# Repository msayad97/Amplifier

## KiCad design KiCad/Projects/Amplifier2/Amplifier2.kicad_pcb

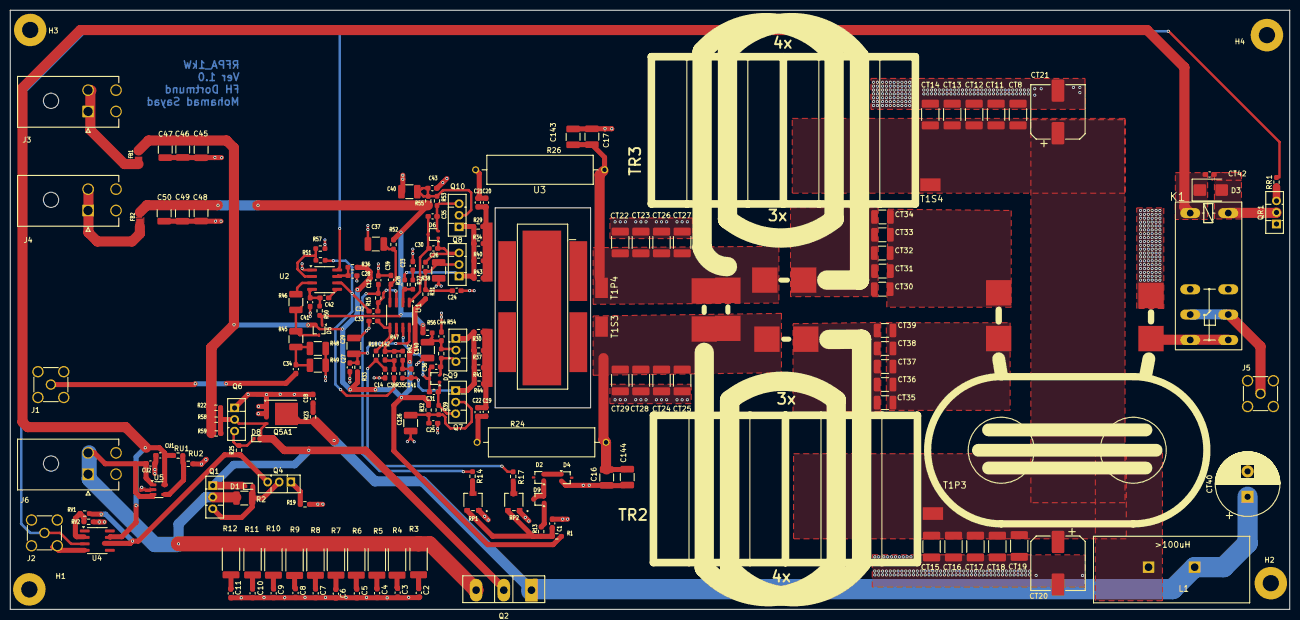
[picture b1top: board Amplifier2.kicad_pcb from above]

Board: 4 copper layers, 252.0 x 118.0 mm, 196 parts (0 on the bottom side), 80 nets.

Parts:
C1, C2, C3, C4, C5, C6, C7, C8, C9, C10, C11, C12, C14, C23, C24, C25, C27, C28, C30, C31, C32, C33, C35, C36, C38, C39, C41, C43, C44: 0.1uF; C_0603_1608Metric_Pad1.08x0.95mm_HandSolder
C16, C17, C143, C144: 470p; C_1210_3225Metric_Pad1.33x2.70mm_HandSolder
C18, C19, C20: 1nF; C_0603_1608Metric_Pad1.08x0.95mm_HandSolder
C21, C22: DNA; C_0603_1608Metric_Pad1.08x0.95mm_HandSolder
C26, C29, C37, C40, C45, C46, C47, C48, C49, C50, C126, C140: 10uF; C_1210_3225Metric_Pad1.33x2.70mm_HandSolder
C34: 4n7; C_0603_1608Metric_Pad1.08x0.95mm_HandSolder
C42, C141: 10p; C_0603_1608Metric_Pad1.08x0.95mm_HandSolder
C142: NDA; C_0603_1608Metric_Pad1.08x0.95mm_HandSolder
CT8, CT11, CT15, CT16: 10n; C_1812_4532Metric_Pad1.57x3.40mm_HandSolder
CT12, CT13, CT17, CT18: 100n; C_1812_4532Metric_Pad1.57x3.40mm_HandSolder
CT14, CT19: 1u; C_1812_4532Metric_Pad1.57x3.40mm_HandSolder
CT20, CT21: 100u/63; CP_Elec_10x10.5
CT22, CT23, CT24, CT25, CT26, CT27, CT28, CT29: 120p; C_1812_4532Metric_Pad1.57x3.40mm_HandSolder
CT30, CT31, CT32, CT33, CT34, CT35, CT36, CT37, CT38, CT39: 10n; C_1210_3225Metric_Pad1.33x2.70mm_HandSolder
CT40: 470u/63; CP_Radial_D12.5mm_P5.00mm
CT42: 100n; C_0603_1608Metric_Pad1.08x0.95mm_HandSolder
CU1, CU2: 1uF; C_0603_1608Metric_Pad1.08x0.95mm_HandSolder
D1, D8: BAT54XV2T5G; D_SOD-523_new
D2, D4, D5, D6, D7, D9: BAV99WT1G; SOT-323_SC-70
D3: D; D_SMB
FB1, FB2: FerriteBead; BLM21PG300SN1B
H1, H2, H3, H4: MountingHole; MountingHole_3.2mm_M3_Pad
J1: Input; SMA_Amphenol_901-144_Vertical
J2: Enable; SMA_Amphenol_901-144_Vertical
J3: Vp_8V; MOLEX_26013115
J4: Vn_-5V; MOLEX_26013115
J5: Output; SMA_Amphenol_901-144_Vertical
J6: Input_56V; MOLEX_26013115
K1: G2RE
L1: >100uH; KERN90_STEHEND_2PIN
Q1, Q4, Q6, Q7, Q8: BD139; TO-126-3_Vertical
Q2: IXTH90P10P; TO-247-3_MOSFET
Q5A1: BSC340N08NS3G; TDSON-8-1
Q9, Q10: BD140; TO-126-3_Vertical
QR1: BD139; TO-126-3_Vertical
R1, R15, R18, R25: 4k7; R_0603_1608Metric_Pad0.98x0.95mm_HandSolder
R2: 330R; R_1210_3225Metric_Pad1.30x2.65mm_HandSolder
R3, R4, R5, R6, R7, R8, R9, R10, R11, R12: 2R2; R_2512_6332Metric_Pad1.40x3.35mm_HandSolder
R13, R14, R17, R19: 120R; R_0603_1608Metric_Pad0.98x0.95mm_HandSolder
R22, R35, R42, R47, R58, R59: 220R; R_0603_1608Metric_Pad0.98x0.95mm_HandSolder
R23, R31, R32, R33, R36, R50, R52, R55, R56: 2R2; R_0603_1608Metric_Pad0.98x0.95mm_HandSolder
R24, R26: 270R; AX_1.000X.225_.034
R27, R28, R51, R57: 470R; R_0603_1608Metric_Pad0.98x0.95mm_HandSolder
R29, R30, R34, R37, R40, R41, R43, R44: 39R; R_0603_1608Metric_Pad0.98x0.95mm_HandSolder
R38, R39, R53, R54: 10k; R_0603_1608Metric_Pad0.98x0.95mm_HandSolder
R45, R46, R48, R49: 100R; R_1210_3225Metric_Pad1.30x2.65mm_HandSolder
RP1, RP2: R_Potentiometer; PVG3A
RR1: 1K; R_0603_1608Metric_Pad0.98x0.95mm_HandSolder
RU1: 25.2k; R_0603_1608Metric_Pad0.98x0.95mm_HandSolder
RU2: 1.35k; R_0603_1608Metric_Pad0.98x0.95mm_HandSolder
RV1: 10k; R_0603_1608Metric_Pad0.98x0.95mm_HandSolder
RV2: 2k; R_0603_1608Metric_Pad0.98x0.95mm_HandSolder
T1P3, T1P4, T1S3, T1S4: THICKPINSMD2,5X4; SMDPAD2,5X4
TR2: DOPPELRINGKERN
TR3: DOPPELRINGKERN_REV
TR4: BALUN; DOPPELLMANTEL_STEHEND
U1: AD8017ARZ; SOIC-8_3.9x4.9mm_P1.27mm
U2: AD8021AR; SOIC-8_3.9x4.9mm_P1.27mm
U3: BLF188XRU; BLF188
U4: AD8033; SOIC-8_3.9x4.9mm_P1.27mm
U5: LT3014xS5; SOT-23-5

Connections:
/HF Part/OutP1: CT30.2, CT31.2, CT32.2, CT33.2, CT34.2, TR3.S2
/HF Part/OutP2: CT35.2, CT36.2, CT37.2, CT38.2, CT39.2, TR2.S2
/HF Part/OutS1: CT30.1, CT31.1, CT32.1, CT33.1, CT34.1, TR4.S2
/HF Part/OutS2: CT35.1, CT36.1, CT37.1, CT38.1, CT39.1, TR4.P2
/HF Part/RFB1: C20.2, C21.2, R26.2
/HF Part/RFB2: C19.2, C22.2, R24.2
/Switch/ENA: Q4.3 (B), R25.1, RV1.1, U4.6
/Switch/G: D1.1 (A), D8.2 (K), Q1.1 (E), Q2.1 (G), Q5A1.4 (G), Q6.2 (C), R22.2, R58.2, R59.2
D1: C17.2, C143.2, CT22.1, CT23.1, CT26.1, CT27.1, R26.1, T1P4.P$1 (1), TR2.P1, TR3.P2, TR3.S1, U3.1 (D1)
D2: C16.2, C144.2, CT24.2, CT25.2, CT28.2, CT29.2, R24.1, T1S3.P$1 (1), TR2.P2, TR2.S1, TR3.P1, U3.2 (D2)
Enable: J2.1 (In), RR1.2, U2.8 (~DISABLE), U4.3 (+)
GND: C1.2, C2.2, C3.2, C4.2, C5.2, C6.2, C7.2, C8.2, C9.2, C10.2, C11.2, C12.2, C14.2, C16.1, C17.1, C18.2, C23.2, C24.2, C25.2, C26.2, C27.2, C28.2, C29.2, C33.1, C37.2, C39.2, C40.2, C41.2, C43.2, C44.2, C45.2, C46.2, C47.2, C48.2, C49.2, C50.2, C126.2, C140.2, C143.1, C144.1, CT8.2, CT11.2, CT12.2, CT13.2, CT14.2, CT15.2, CT16.2, CT17.2, CT18.2, CT19.2, CT20.2, CT21.2, CT22.2, CT23.2, CT24.1, CT25.1, CT26.2, CT27.2, CT28.1, CT29.1, CT40.2, CU1.2, CU2.2, D4.2 (A), J1.2 (Ext), J2.2 (Ext), J3.3, J3.4, J4.3, J4.4, J5.2 (Ext), J6.3, J6.4, K1.O0 (O), K1.O1 (O@1), Q5A1.1 (S), Q5A1.2 (S), Q5A1.3 (S), Q6.1 (E), QR1.1 (E), R19.2, R48.2, R49.2, R57.1, RP1.3, RP2.3, RU2.2, RV2.2, TR4.S1, U2.1 (LOGIC_REFERENCE), U3.5 (S), U4.4 (V-), U5.2 (GND)
Input_56V: CU2.1, J6.1, J6.2, Q1.2 (C), Q2.3 (S), R2.1, R3.1, R4.1, R5.1, R6.1, R7.1, R8.1, R9.1, R10.1, R11.1, R12.1, U5.1 (VIN), U5.3 (~SHDN)
Input_Signal: C34.1, J1.1 (In)
unnamed: C1.1, R1.1, R13.1, RP1.1, RP2.1
unnamed: C2.1, R3.2
unnamed: C3.1, R4.2
unnamed: C4.1, R5.2
unnamed: C5.1, R6.2
unnamed: C6.1, R7.2
unnamed: C7.1, R8.2
unnamed: C8.1, R9.2
unnamed: C9.1, R10.2
unnamed: C10.1, R11.2
unnamed: C11.1, R12.2
unnamed: C12.1, R14.1, R15.2
unnamed: C14.1, R17.1, R18.2
unnamed: C18.1, R23.2
unnamed: C23.1, R27.1
unnamed: C34.2, R45.2, R48.1, R49.1
unnamed: C141.1, R35.2, R42.1
unnamed: C38.2, C142.1, R47.2
unnamed: D1.2 (K), Q1.3 (B), Q4.2 (C), R2.2
unnamed: D2.2 (A), D4.1 (K)
unnamed: CT42.2, D3.2 (A), K1.2, QR1.2 (C)
unnamed: D5.3 (K), R45.1, R46.2
unnamed: C35.2, D6.2 (A), Q10.3 (B), R53.1
unnamed: C36.2, D7.2 (A), Q9.3 (B), R54.1
unnamed: D8.1 (A), Q6.3 (B), R25.2
unnamed: D2.1 (K), D9.2 (A), D9.3 (K)
unnamed: D9.1 (K), R13.2
unnamed: FB1.2, J3.1, J3.2
unnamed: FB2.2, J4.1, J4.2
unnamed: J5.1 (In), K1.P0 (P@1), K1.P1
unnamed: K1.S0 (S), K1.S1 (S@1), TR4.P1
unnamed: CT8.1, CT11.1, CT12.1, CT13.1, CT14.1, CT15.1, CT16.1, CT17.1, CT18.1, CT19.1, CT20.1, CT21.1, L1.P$2 (2), T1P3.P$1 (1), T1S4.P$1 (1)
unnamed: Q4.1 (E), R19.1
unnamed: C31.2, D7.1 (K), Q7.3 (B), R39.2
unnamed: C25.1, C126.1, Q7.2 (C), R32.1, R39.1
unnamed: C141.2, Q7.1 (E), Q9.1 (E), R30.2, R35.1, R37.2, R41.2, R44.2
unnamed: C30.2, D6.1 (K), Q8.3 (B), R38.2
unnamed: C24.1, C26.1, Q8.2 (C), R31.1, R38.1
unnamed: C44.1, C140.1, Q9.2 (C), R54.2, R56.1
unnamed: C40.1, C43.1, Q10.2 (C), R53.2, R55.1
unnamed: Q8.1 (E), Q10.1 (E), R28.2, R29.2, R34.2, R40.2, R43.2
unnamed: QR1.3 (B), RR1.1
unnamed: R14.2, RP1.2
unnamed: R17.2, RP2.2
unnamed: C27.1, C29.1, R33.1, U1.8 (+VS)
unnamed: R27.2, R28.1, U1.2 (-IN1)
unnamed: C142.2, R42.2, R47.1, U1.6 (-IN2)
unnamed: C37.1, C39.1, R52.1, U1.4 (-VS)
unnamed: C30.1, C35.1, D6.3 (K), U1.1 (OUT1)
unnamed: C31.1, C36.1, D7.3 (K), U1.7 (OUT2)
unnamed: R46.1, U2.3 (+)
unnamed: R51.1, R57.2, U2.2 (-)
unnamed: C42.1, U2.5 (C_{COMP})
unnamed: C28.1, R36.1, U2.7 (V+)
unnamed: C41.1, C42.2, R50.1, U2.4 (V-)
unnamed: RV1.2, RV2.1, U4.2 (-)
unnamed: RU1.2, RU2.1, U5.4 (ADJ)
Output_56V: CT40.1, L1.P$1 (1), Q2.2 (D), Q5A1.5 (D), R23.1
Output_OPV1: C32.1, C38.1, R51.2, U2.6
Output_OPV2_1: C20.1, C21.1, R29.1, R34.1, R40.1, R43.1, U3.3 (G1)
Output_OPV2_2: C19.1, C22.1, R30.1, R37.1, R41.1, R44.1, U3.4 (G2)
V_25V: CT42.1, CU1.1, D3.1 (K), K1.1, RU1.1, U4.7 (V+), U5.5 (VOUT)
Vn: C48.1, C49.1, C50.1, D5.1 (K), FB2.1, R50.2, R52.2, R55.2, R56.2
Vp: C45.1, C46.1, C47.1, D5.2 (A), FB1.1, R1.2, R22.1, R31.2, R32.2, R33.2, R36.2, R58.1, R59.1
bias1: C32.2, R15.1, U1.3 (+IN1)
bias2: C33.2, R18.1, U1.5 (+IN2)

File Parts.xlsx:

Name | Zahl | Value | Footprint | Link
Q2 | 1 | IXTH90P10P | TO247AA | https://www.mouser.de/ProductDetail/IXYS/IXTH90P10P?qs=cvHLL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
Q5 | 1 | BSC340N08NS3 | SO8_N | https://www.mouser.de/ProductDetail/Infineon-Technologies/BS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
Q1, Q4, Q6, Q7, Q8, QR1 | 6 | BD139 | SOT-32 | https://www.mouser.de/ProductDetail/STMicroelectronics/BD139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
Q9, Q10 | 2 | BD140 | SOT-32 | https://www.mouser.de/ProductDetail/STMicroelectronics/BD140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
D1, D8 | 2 | BAT54XV2T5G | ONSC-SOD-523 | https://www.mouser.de/ProductDetail/onsemi/BAT54XV2T5G?qs=Jh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
D2, D4, D5, D6, D7, D9 | 6 | BAV99WT1G | ONSC-SOT-323_SC-70 | https://www.mouser.de/ProductDetail/onsemi/BAV99WT1G?qs=vLkC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
D3 | 1 | Schottky Diode | SMA
U1 | 1 | AD8017ARZ | SOIC-8_3.9x4.9mm | https://www.mouser.de/ProductDetail/Analog-Devices/AD8017ARZ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
U2 | 1 | AD8021ARZ | SOIC-8_3.9x4.9mm | https://www.mouser.de/ProductDetail/Analog-Devices/AD8021ARZ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
U3 | 1 | BLF188XRU | SOT-539A | https://www.digikey.de/de/products/detail/ampleon-usa-inc/56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
U4 | 1 | AD8033 | SOIC-8_3.9x4.9mm | https://www.mouser.de/ProductDetail/Analog-Devices/AD8033ARZ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
U5 | 1 | LT3014xS5 | SOT-23-5 | https://www.mouser.de/ProductDetail/Analog-Devices/LT3014ES5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
U6 | 1 | LT1085-12 | SOT_THT:TO-220-3 | https://www.mouser.de/ProductDetail/Analog-Devices/LT1085CT-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
J3, J4, J6 | 3 | Molex Stecker | MOLEX_26013115 | https://www.mouser.de/ProductDetail/Molex/26-01-3115?qs=ZhwK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
J1, J2, J5 | 3 | Connector_Coaxial | SMA_Amphenol_901-144_Vertical | https://www.mouser.de/ProductDetail/Amphenol-RF/901-144?qs=a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
K1 | 1 | G5RL-1A-E-HR-DC12 |  | https://www.mouser.de/ProductDetail/Omron-Electronics/G5RL-1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
L1 | 1 | Ferrite Ring | 74270115 | https://www.mouser.de/ProductDetail/Wurth-Elektronik/7427011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
TR1-TR4 | 8 | Ferrite Core | 875-28B0562-100 | https://www.mouser.de/ProductDetail/Laird-Performance-Materi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
Koaxialkabel |  |  |  | https://www.digikey.de/de/products/filter/koaxialkabel-hf/47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
Ferrite Bead | sind vorhanden ?
FB1, FB2 | 2 | BLM21PG300SN1B | SMD/SMT | https://www.mouser.de/ProductDetail/Murata-Electronics/BLM21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
Resistors | sind vorhanden ?
R1, R15, R18, R25 | 4 | 4k7 | SM/R_0603
R23, R31, R32, R33, R36, R50, R52, R55, R56 | 9 | 2R2 | SM/R_0603
R27, R28, R51, R57 | 4 | 470R | SM/R_0603
R13, R14, R17 | 3 | 120R | SM/R_0603
R29, R30 R34, R37, R40, R41, R43, R44 | 8 | 39R | SM/R_0603
RR1 | 1 | 1k | SM/R_0603
RV1 | 1 | 2k | SM/R_0603
RV2, R38, R38, R53, R54 | 5 | 10k | SM/R_0603
RU1 | 1 | 25.2k | SM/R_0603
RU2 | 1 | 1.35k | SM/R_0603
Sum | 36 |  | SM/R_0603
R22, R58, R59 | 3 | 220R/0.5W | SM/R_1210
R2 | 1 | 30R/0.5W | SM/R_1210
R45, R46, R48, R49 | 4 | 100R | SM/R_1210
R19 | 1 | 120R | SM/R_1210
R35, R42, R47 | 3 | 220R | SM/R_1210
Sum | 12 |  | SM/R_1210
R3 - R12 | 10 | 2R2 | SMD/R_2512
Sum | 10 |  | SMD/R_2512
R24, R26 | 2 | 270R |  | https://www.mouser.de/ProductDetail/Vishay-Beyschlag/MBA0204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
RP1, RP2 | 2 | PCG3A504C01R00 | SMD/SMT | https://www.mouser.de/ProductDetail/Bourns/PVG3A504C01R00?qs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
Capacitors | sind vorhanden ? |  |  | https://www.mouser.de/ProductDetail/KEMET/EEV107M063A9PAA?qs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
CT20, CT21 | 2 | 100u/63 |  | https://www.mouser.de/ProductDetail/Panasonic/ECA-1JM471?qs=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
CT40 | 1 | 470/63
C42 | 1 | 10p | SM/C_0603
C34 | 1 | 4n7 | SM/C_0603
C18, C19, C20. CU1, CU2 | 5 | 1nF | SM/C_0603
C1 - C12, C14, C23, C24, C25, C27, C30, C31, C32, C33, C36, C38, C39, C28, C41,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 | 28 | 0.1uF | SM/C_0603
CU3 | 1 | 10uF | SM/C_0603
CU4 | 1 | 10uF | SM/C_0603
C21, C22, C142 | 3 | DNA | SM/C_0603
Sum | 34 |  | SM/C_0603
C16, C17, C143, C144 | 4 | 470p | SM/C_1210
CT30 - CT 39 | 10 | 10n | SM/C_1210
C26, C29, C37, C40, C45 - C50, C126, C140 | 12 | 10uF | SM/C_1210
Sum | 26 |  | SM/C_1210
CT22 - CT29 | 8 | 120p | SM/C_1812
CT8, CT11, CT15, CT16 | 4 | 10n | SM/C_1812
CT12, CT13, CT17, CT18 | 4 | 100n | SM/C_1812
CT14, CT19 | 2 | 1u | SM/C_1812
Sum | 18 |  | SM/C_1812

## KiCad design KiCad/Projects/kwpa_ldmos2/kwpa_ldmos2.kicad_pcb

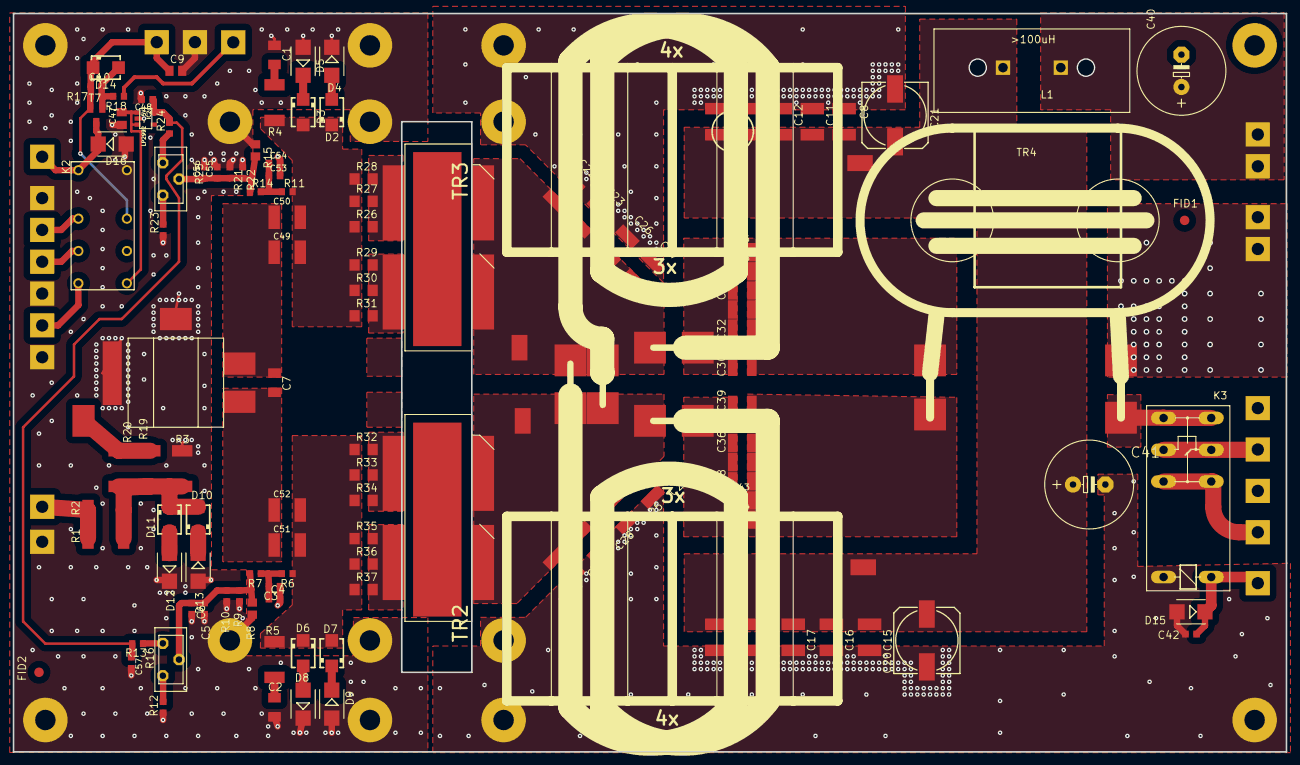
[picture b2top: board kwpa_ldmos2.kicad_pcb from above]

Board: 2 copper layers, 200.0 x 116.0 mm, 161 parts (0 on the bottom side), 49 nets.

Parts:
C1, C2: 10n/450V; C1206K
C3, C5, C53, C55, C57: 1u; C0603K
C4, C42, C54: 100n; C0603K
C6, C10, C56: 10n; C0603K
C7: opt.; C1206K
C8, C11, C15, C16: 10n; C1812K
C9: 10u/25; C0805K
C12, C13, C17, C18, C49, C50, C51, C52: 100n; C1812K
C14, C19: 1u; C1812K
C20, C21: 100u/63; 153CLV-1014
C22, C23, C24, C25, C26, C27, C28, C29: 120p; C1812K
C30, C31, C32, C33, C34, C35, C36, C37, C38, C39, C43, C44, C45, C46: 10n; C1210K
C40, C41: 470uF/63V; E5-13
C47: 10u; C0805K
C48: 10u; C0603K
D2, D6: 8,2V; SMA
D3, D7: 4,7V; SMA
D4, D5, D8, D9, D12, D13, D15, D16: DIODE SMB; SMB
D10, D11: SMBJ15A; SMA
D14: 6,2V/1W; SMA
FID1, FID2: FIDUCIAL
H1, H2, H3, H4, H5, H6, H7, H8, H9, H10, H11, H12, H13, H14: HOLE_32; HOLE32
IC2: LP2992 - 5V; SOT23-5
JP1: RF_IN; THICKPIN
JP2, JP3, JP8, JP10, JP12, JP14, JP15, JP20, JP22: GND; THICKPIN
JP4: RXBYP-2; THICKPIN
JP5: +12..+14V; THICKPIN
JP7: RX_BYP1; THICKPIN
JP9: PTT; THICKPIN
JP11: RF-OUT; THICKPIN
JP13, JP16: +50V; THICKPIN
JP17, JP18: RELAIS; THICKPIN
JP19: TO_ATT; THICKPIN
JP21: FROM_ATT; THICKPIN
K2: FINDER-30.22
K3: G5RL-1E-HR-12V; G2RE
L1: >100uH; KERN90_STEHEND_2PIN
R1, R2, R19, R20: 22/2W; R2512
R3: 100/2W; R2512
R4, R5: 10/2W; R2512
R6, R11: 1k; R0603
R7, R14: 470; R0603
R8, R15: NTC0805J5K0; R0805
R9, R21: 560; R0603
R10, R22: 5k6; R0603
R12, R23: 47; R0603
R13, R24: 270; R0603
R16, R25: 250; MINIPOTI
R17, R18: 10k; R0603
R26, R27, R28, R29, R30, R31, R32, R33, R34, R35, R36, R37: 10; R1206
T1, T2: BLF188
T1P3, T1P4, T1S3, T1S4: SMDPAD2,5X4
T7: IRLML6401; SOT23
TR1: 4:1 Laird 28B0562-100; KW-INPUT_LAIRD_28B0562-100
TR2: DOPPELRINGKERN
TR3: DOPPELRINGKERN_REV
TR4: DOPPELLMANTEL_STEHEND

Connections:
ATTM: D10.A, D11.C, R1.2, R2.2, R3.2, R19.1, R20.1
BYP1: JP7.1, K2.12
DD1: C49.2, C50.2, D2.C, D3.A, R4.1, R11.2, R26.1, R27.1, R28.1, R29.1, R30.1, R31.1
DD2: C51.2, C52.2, D6.C, D7.A, R5.2, R6.2, R32.1, R33.1, R34.1, R35.1, R36.1, R37.1
DI1: C7.1, C49.1, C50.1, TR1.OUT2
DI2: C7.2, C51.1, C52.1, TR1.OUT1
DRAIN1: C22.2, C23.2, C26.2, C27.2, T1P4.P$1, T2.1, T2.2, TR2.P1, TR3.P2, TR3.S1
DRAIN2: C24.2, C25.2, C28.2, C29.2, T1.1, T1.2, T1S3.P$1, TR2.P2, TR2.S1, TR3.P1
G1: R26.2, R27.2, R28.2, T2.3
G2: R29.2, R30.2, R31.2, T2.4
G3: R32.2, R33.2, R34.2, T1.3
G4: R35.2, R36.2, R37.2, T1.4
GND: C1.1, C2.2, C3.2, C4.2, C5.2, C6.2, C8.2, C9.2, C11.2, C12.2, C13.2, C14.2, C15.1, C16.1, C17.1, C18.1, C19.1, C20.-, C21.-, C22.1, C23.1, C24.1, C25.1, C26.1, C27.1, C28.1, C29.1, C40.-, C41.-, C42.1, C47.1, C48.2, C53.2, C54.2, C55.2, C56.2, C57.2, D4.C, D5.A, D8.C, D9.A, D12.C, D13.A, D15.A, D16.A, H1.P$1, H2.P$1, H3.P$1, H4.P$1, H5.P$1, H6.P$1, H7.P$1, H8.P$1, H9.P$1, H10.P$1, H11.P$1, H12.P$1, H13.P$1, H14.P$1, IC2.2, JP2.1, JP3.1, JP8.1, JP10.1, JP12.1, JP14.1, JP15.1, JP20.1, JP22.1, K2.A2, K3.2, R3.1, R8.1, R9.1, R10.1, R12.1, R15.1, R21.1, R22.1, R23.1, TR1.COM, TR1.GND, TR4.S1
unnamed: JP21.1, R1.1, R2.1
unnamed: C47.2, IC2.1, IC2.3, K2.24
unnamed: D10.C, D13.C
unnamed: JP11.1, K3.P0, K3.P1
unnamed: C1.2, R4.2
unnamed: C2.1, R5.1
unnamed: JP19.1, K2.14
unnamed: C3.1, C4.1, R6.1, R7.2
unnamed: C5.1, C6.1, R7.1, R8.2, R9.2, R10.2, R16.3
unnamed: R12.2, R16.2
unnamed: R13.1, R16.1
unnamed: C48.1, C57.1, IC2.5, R13.2, R24.2
unnamed: D3.C, D5.C
unnamed: D2.A, D4.A
unnamed: C53.1, C54.1, R11.1, R14.2
unnamed: D7.C, D9.C
unnamed: D6.A, D8.A
unnamed: D11.A, D12.A
unnamed: C55.1, C56.1, R14.1, R15.2, R21.2, R22.2, R25.3
unnamed: R23.2, R25.2
unnamed: R24.1, R25.1
unnamed: C10.2, D14.A, R17.2, R18.2, T7.1
unnamed: JP4.1, K3.O0, K3.O1
unnamed: JP9.1, R18.1
unnamed: R19.2, R20.2, TR1.IN
OUTP1: C30.1, C31.1, C32.1, C33.1, C34.1, C45.1, C46.1, TR3.S2
OUTP2: C35.1, C36.1, C37.1, C38.1, C39.1, C43.1, C44.1, TR2.S2
OUTR1: K3.S0, K3.S1, TR4.P1
OUTS1: C30.2, C31.2, C32.2, C33.2, C34.2, C45.2, C46.2, TR4.S2
OUTS2: C35.2, C36.2, C37.2, C38.2, C39.2, C43.2, C44.2, TR4.P2
RELAIS: C42.2, D15.C, JP18.1, K3.1
RELAISOUT: D16.C, JP17.1, K2.A1, T7.3
RFIN: JP1.1, K2.11
U12: C9.1, C10.1, D14.C, JP5.1, K2.21, R17.1, T7.2
UIN: C40.+, JP13.1, JP16.1, L1.P$1
UVERS: C8.1, C11.1, C12.1, C13.1, C14.1, C15.2, C16.2, C17.2, C18.2, C19.2, C20.+, C21.+, C41.+, L1.P$2, T1P3.P$1, T1S4.P$1

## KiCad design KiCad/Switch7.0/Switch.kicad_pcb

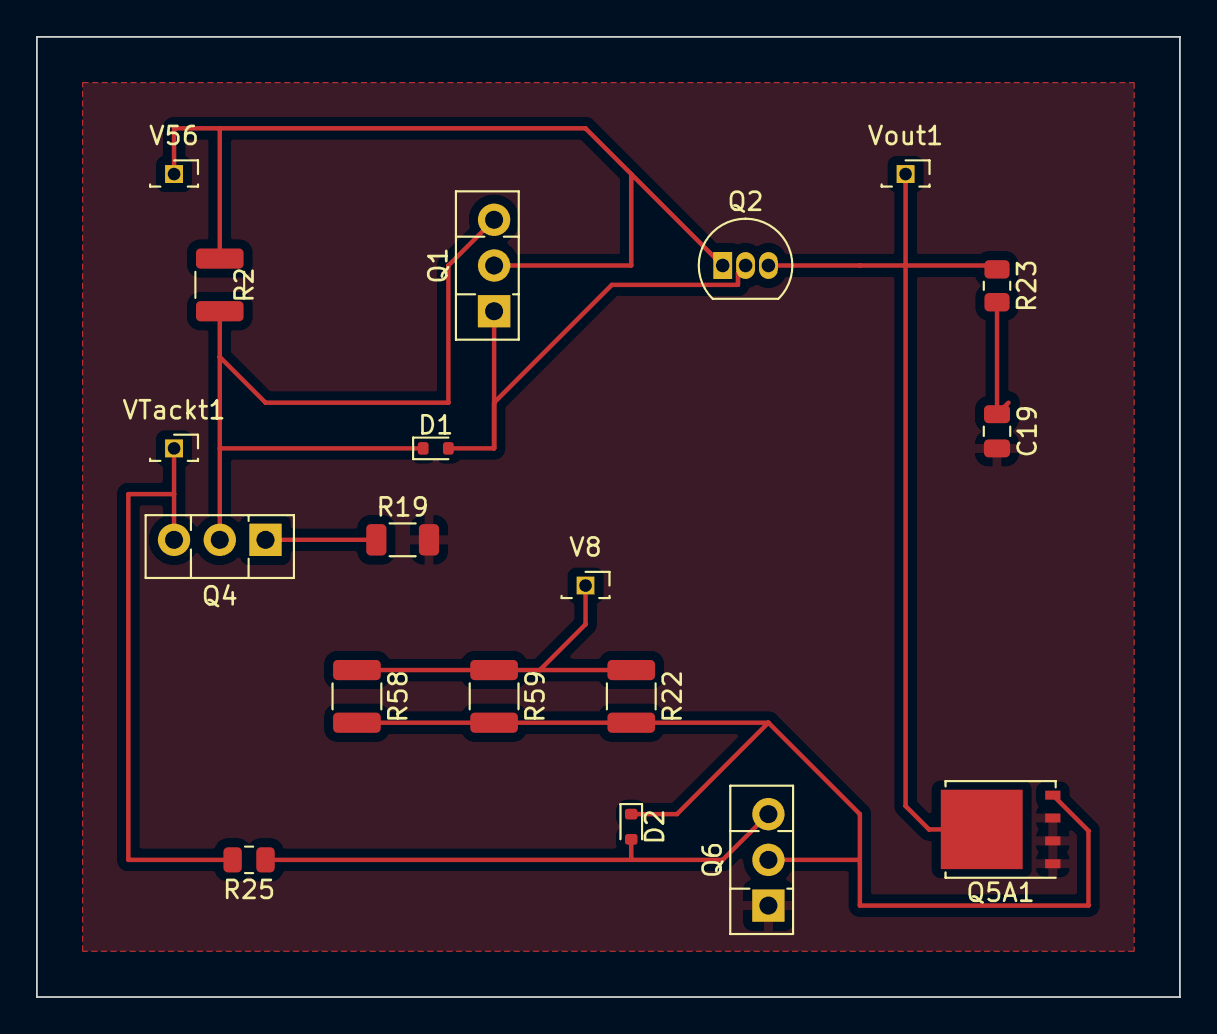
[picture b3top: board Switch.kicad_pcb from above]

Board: 2 copper layers, 63.5 x 53.3 mm, 19 parts (0 on the bottom side), 11 nets.

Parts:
C19: 1nF; C_0805_2012Metric
D1, D2: BAT54XV2T5G; D_SOD-523
Q1, Q4, Q6: BD139; TO-126-3_Vertical
Q2: IXTH90P10P; TO-92_Inline
Q5A1: BSC340N08NS3G; TDSON-8-1
R2: 330R; R_1210_3225Metric
R19: 120R; R_1206_3216Metric
R22, R58, R59: 220R; R_1210_3225Metric
R23: 2R2; R_0805_2012Metric
R25: 4k7; R_0805_2012Metric
V8, V56: Conn_01x01_Socket; PinSocket_1x01_P1.27mm_Vertical
VTackt1: Conn_01x01_Socket; PinSocket_1x01_P1.27mm_Vertical
Vout1: Conn_01x01_Socket; PinSocket_1x01_P1.27mm_Vertical

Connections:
GND: C19.2, Q5A1.1 (S), Q5A1.2 (S), Q5A1.3 (S), Q6.1 (E), R19.2
unnamed: C19.1, R23.2
unnamed: D1.2 (A), Q1.1 (E), Q2.2 (G)
unnamed: D1.1 (K), Q1.3 (B), Q4.2 (C), R2.2
unnamed: D2.2 (A), Q6.3 (B), R25.1
unnamed: D2.1 (K), Q5A1.4 (G), Q6.2 (C), R22.2, R58.2, R59.2
unnamed: Q1.2 (C), Q2.1 (D), R2.1, V56.1
unnamed: Q2.3 (S), Q5A1.5 (D), R23.1, Vout1.1
unnamed: Q4.3 (B), R25.2, VTackt1.1
unnamed: Q4.1 (E), R19.1
unnamed: R22.1, R58.1, R59.1, V8.1

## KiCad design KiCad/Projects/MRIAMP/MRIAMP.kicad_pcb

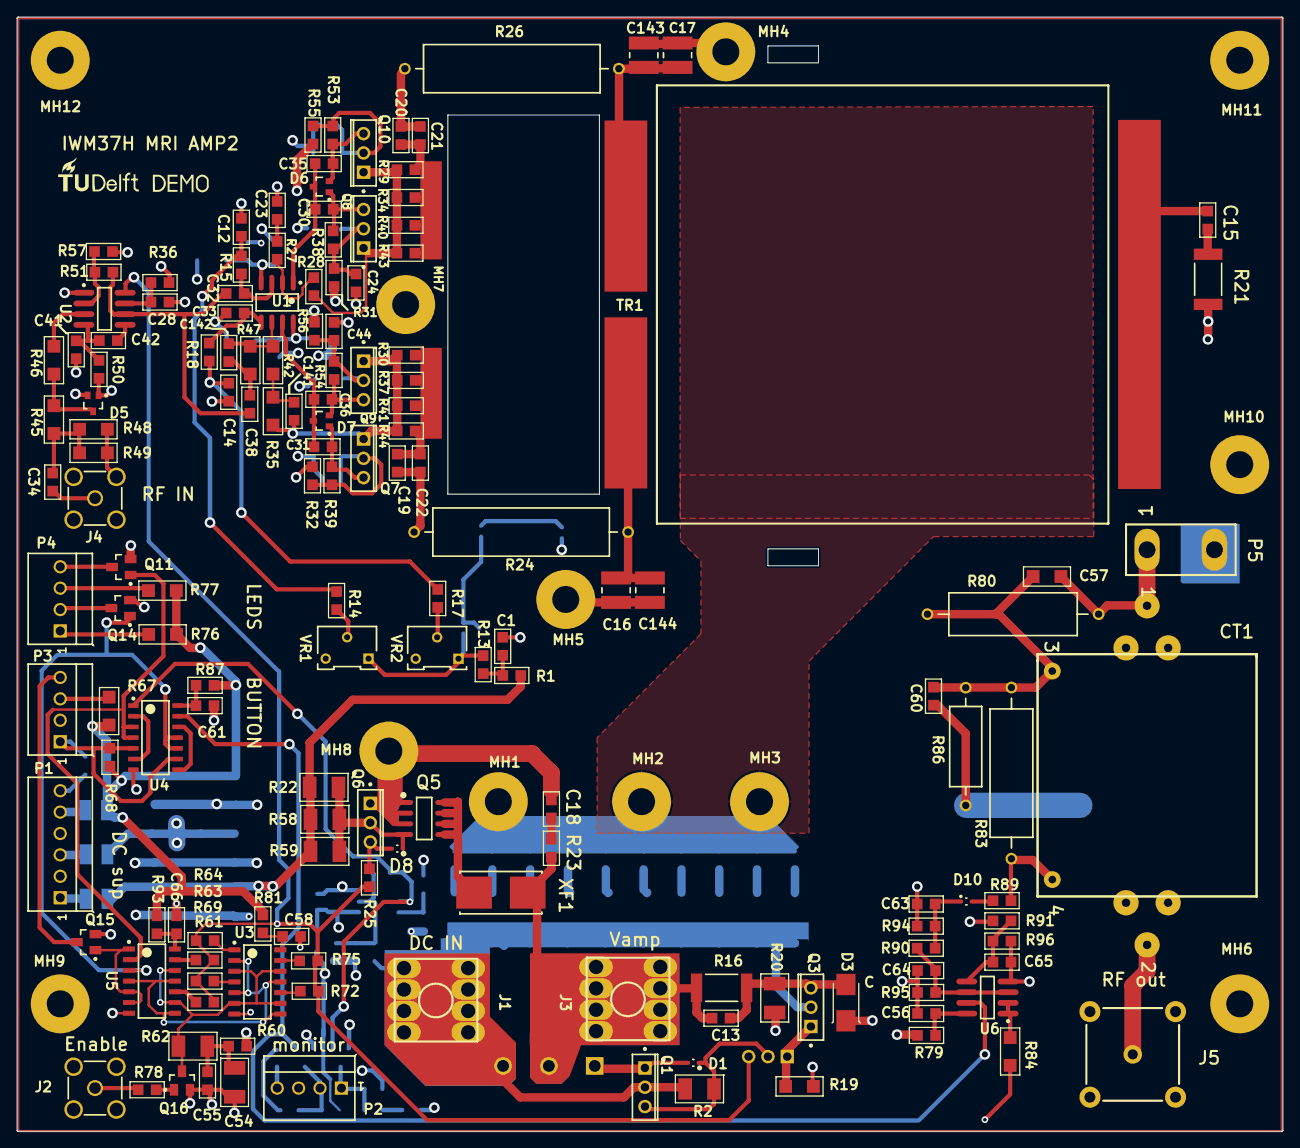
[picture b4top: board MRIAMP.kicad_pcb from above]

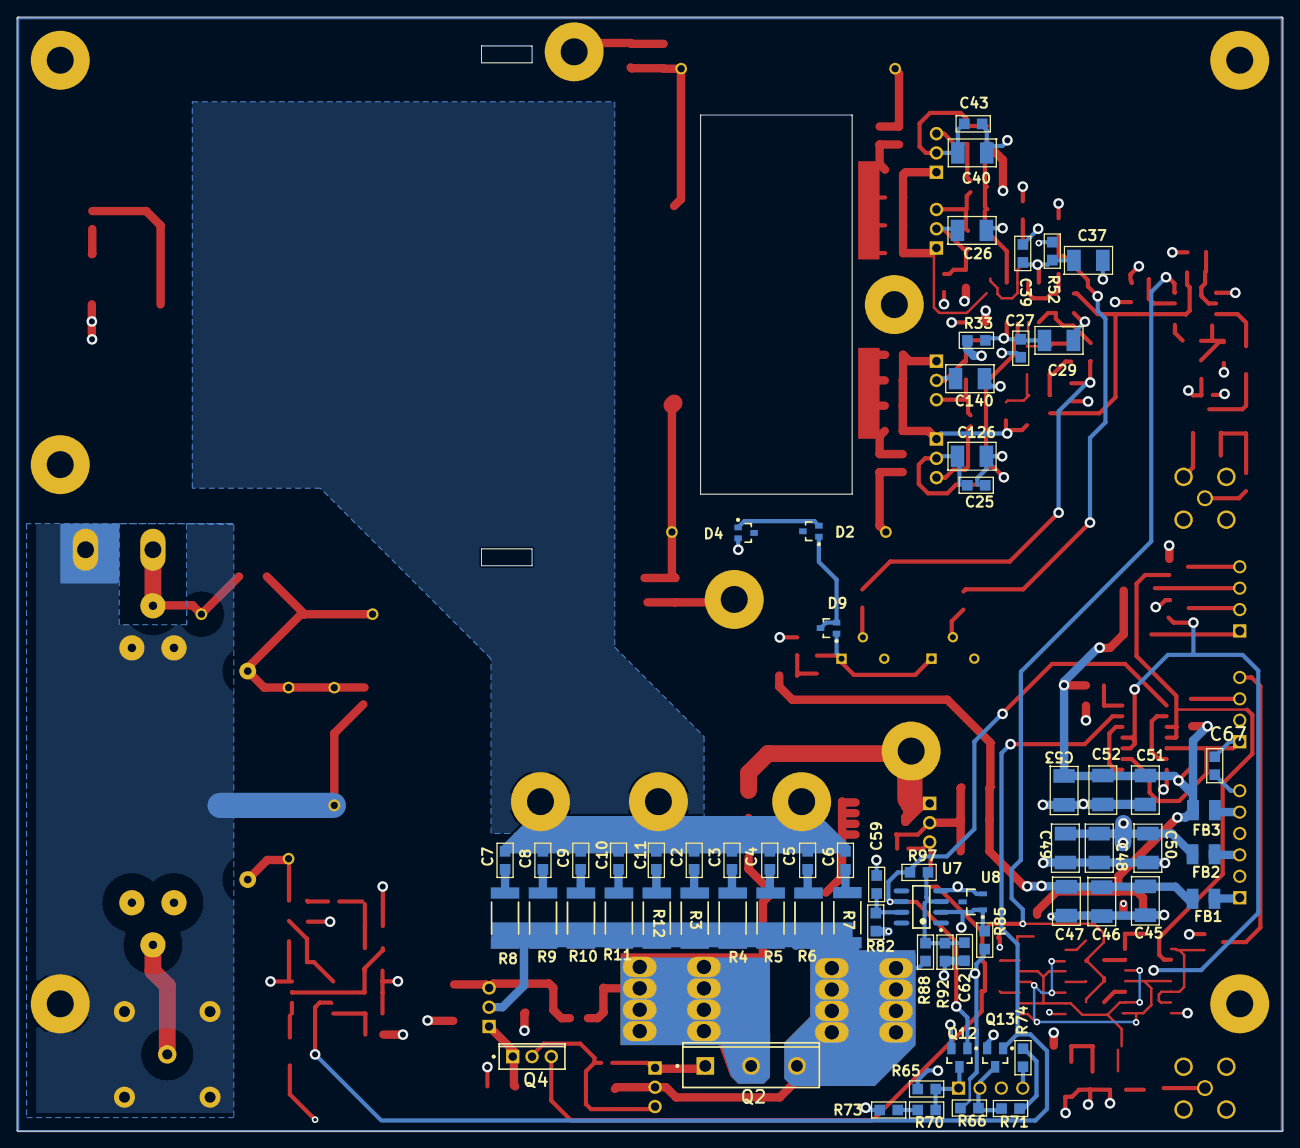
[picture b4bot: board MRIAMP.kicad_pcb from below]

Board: 4 copper layers, 150.3 x 132.3 mm, 235 parts (68 on the bottom side), 124 nets.

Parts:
C1, C2, C3, C4, C5, C6, C7, C8, C9, C10, C11, C12, C13, C14, C15, C18, C19, C20, C21, C22, C23, C24, C25, C27, C28, C30, C31, C32, C33, C34, C35, C36, C38, C39, C41, C42, C43, C44, C55, C56, C58, C59, C60, C61, C62, C63, C64, C65, C66, C67, C141, C142: Cap; SM/C_0805
C16, C17, C143, C144: Cap; SMD/C_1111
C26, C29, C37, C40, C45, C46, C47, C48, C49, C50, C51, C52, C53, C54, C126, C140: Cap; SM/C_1210
C57: Cap; SM/C_1206
CT1: CT1:10; CT
D1, D8, D10: BAT54XV2T5G; ONSC-SOD-523-2-502-01_V
D2, D4, D5, D6, D7, D9: BAV99WT1G; ONSC-SOT-323-3-419-04_V
D3: ES1C; SM/DO214AC_12
FB1, FB2, FB3: BLM21PG300SN1B; MURA-BLM21-B40-CHIP-2_V1
IWM37H MRI AMP2: Comment; LOGO3
J1, J3: M4 bushing; BUSHING_M4
J2, J4: CONSMA008; SMA-Grotere-Gaten
J5: R141426161; BNC_Danny
MH1, MH2, MH3, MH4, MH5, MH6, MH7, MH8, MH9, MH10, MH11, MH12: M3spacer; MTHOLE3.2MM_TOPBOT7MM
P1: Header 6; POLCON.100/VH/TM1SQS/W.300/6
P2, P3, P4: HEADER 4; POLCON.100/VH/TM1SQS/W.300/4
P5: RFin; megaheader
Q1, Q3, Q4, Q6, Q7, Q8: BD139; ONSC-TO-225-3-77-09
Q2: IXTH90P10P; INF-PG-TO247-3-44
Q5: BSC340N08NS3; SO8_N
Q9, Q10: BD140; ONSC-TO-225-3-77-09
Q11, Q12, Q13, Q14, Q15, Q16: FDV301N; FAIR-SOT23-3_V
R1, R13, R14, R15, R17, R18, R23, R25, R27, R28, R29, R30, R31, R32, R33, R34, R36, R37, R38, R39, R40, R41, R43, R44, R50, R51, R52, R53, R54, R55, R56, R57, R60, R61, R63, R64, R65, R66, R68, R69, R70, R71, R72, R73, R74, R75, R78, R79, R81, R82, R85, R87, R88, R89, R90, R91, R92, R93, R94, R95, R96, R97: Res2; SM/R_0805
R2, R20, R22, R58, R59, R62: Res2; SM/R_1210
R3, R4, R5, R6, R7, R8, R9, R10, R11, R12, R16, R21: Res2; SMD/R_2512
R19: Res2; SM/R_1206
R24, R26: Res2; AX/1.000X.225/.034
R35, R42, R45, R46, R47, R48, R49, R67, R76, R77, R84: Res2; SM/C_1206
R80, R83: Res2; AX/.800X.200/.037
R86: Res2; AX/.550X.150/.034
TR1: 1:1:4:4; PCBComponent_1
U1: AD8017ARZ; ADI-R-8_L
U2: AD8021ARZ; ADI-R-8_M
U3, U5: SN74HC02D; D0014A_N
U4: SN74AHCT132D; D0014A_L
U6: AD822ARZ; ADI-R-8_M
U7: AD820ARZ; ADI-R-8_L
U8: LM4040CIM3-2.5; DBZ0003A_N
VR1, VR2: 10k; VRES38
XF1: 0154010.DR; LFUS-154_V

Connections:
BIAS1: C32.1, R15.1, U1.3
BIAS2: C33.1, R18.1, U1.5
DCok: Q12.1, R97.2, U4.1, U7.6
DRAIN1: C17.2, C143.2, R26.2, TR1.1
DRAIN2: C16.2, C144.2, R24.2, TR1.3
ENABLE: Q4.3, R25.2, R61.2, R63.2, R64.2, R69.2, R72.2, R75.2, U2.8
GATE1: C20.1, C21.1, R29.2, R34.2, R40.2, R43.2
GATE2: C19.1, C22.1, R30.2, R37.2, R41.2, R44.2
GND: C1.1, C12.1, C14.1, C18.1, C23.1, C24.1, C25.1, C26.2, C27.1, C28.1, C29.2, C33.2, C37.2, C39.2, C40.1, C41.1, C43.2, C44.2, C45.2, C46.2, C47.2, C48.2, C49.2, C50.2, C51.2, C52.2, C53.2, C54.2, C55.1, C56.1, C58.1, C59.1, C61.1, C62.1, C63.1, C64.1, C65.1, C66.1, C67.1, C126.2, C140.1, D3.1, D4.2, J2.2, J2.3, J2.4, J2.5, J4.2, J4.3, J4.4, J4.5, MH7.1, MH8.1, P1.2, P1.4, P1.6, P2.4, P3.2, Q5.1, Q5.2, Q5.3, Q6.1, Q11.2, Q12.2, Q13.2, Q14.2, Q15.2, Q16.2, R19.1, R20.1, R21.2, R48.1, R49.1, R57.1, R73.2, R74.2, R92.2, R94.2, R95.1, R96.1, U2.1, U3.7, U4.7, U5.7, U6.4, U7.4, U8.2, VR1.3, VR2.3
LEDactive: P3.4, Q15.3
LEDdcfail: P4.4, Q11.3
LEDprfl: P4.2, Q14.3
NetC1_2: C1.2, R1.1, R13.2
NetC2_1: C2.1, C3.1, C4.1, C5.1, C6.1, C7.1, C8.1, C9.1, C10.1, C11.1, MH1.1, MH2.1, MH3.1
NetC2_2: C2.2, R3.1
NetC3_2: C3.2, R4.1
NetC4_2: C4.2, R5.1
NetC5_2: C5.2, R6.1
NetC6_2: C6.2, R7.1
NetC7_2: C7.2, R8.1
NetC8_2: C8.2, R9.1
NetC9_2: C9.2, R10.1
NetC10_2: C10.2, R11.1
NetC11_2: C11.2, R12.1
NetC12_2: C12.2, R14.1, R15.2
NetC13_1: C13.1, D3.2, Q3.3, R16.2, R20.2
NetC14_2: C14.2, R17.1, R18.2
NetC15_1: C15.1, TR1.2
NetC15_2: C15.2, R21.1
NetC16_1: C16.1, C144.1, MH5.1
NetC17_1: C17.1, C143.1, MH4.1
NetC18_2: C18.2, R23.1
NetC23_2: C23.2, R27.1
NetC24_2: C24.2, C26.1, Q8.2, R31.1, R38.1
NetC25_2: C25.2, C126.1, Q7.2, R32.2, R39.1
NetC27_2: C27.2, C29.1, R33.1, U1.8
NetC28_2: C28.2, R36.1, U2.7
NetC30_1: C30.1, D6.1, Q8.3, R38.2
NetC30_2: C30.2, C35.2, D6.3, U1.1
NetC31_1: C31.1, D7.1, Q7.3, R39.2
NetC31_2: C31.2, C36.2, D7.3, U1.7
NetC32_2: C32.2, C38.1, R51.2, U2.6
NetC34_2: C34.2, J4.1
NetC35_1: C35.1, D6.2, Q10.3, R53.1
NetC36_1: C36.1, D7.2, Q9.3, R54.1
NetC37_1: C37.1, C39.1, R52.1, U1.4
NetC38_2: C38.2, C142.2, R47.2
NetC40_2: C40.2, C43.1, Q10.2, R53.2, R55.1
NetC41_2: C41.2, C42.2, R50.1, U2.4
NetC42_1: C42.1, U2.5
NetC44_1: C44.1, C140.2, Q9.2, R54.2, R56.2
NetC54_1: C54.1, C55.2, R60.2, R62.2
NetC56_2: C56.2, R79.2, U6.8
NetC57_1: C57.1, C60.2, CT1.3, R80.2, R83.2, R86.1
NetC57_2: C57.2, CT1.1, P5.1, R80.1
NetC58_2: C58.2, R81.2, U3.14
NetC59_2: C59.2, R82.2, U7.7
NetC61_2: C61.2, R87.2, U4.14
NetC62_2: C62.2, R88.2, R92.1, R97.1, U7.3
NetC63_2: C63.2, D10.1, R90.1, R94.1
NetC64_2: C64.2, R90.2, R95.2, U6.3, U6.6
NetC65_2: C65.2, R91.2, R96.2, U6.5
NetC66_2: C66.2, R93.2, U5.14
NetC67_2: C67.2, P3.1, R68.2, U4.5, U4.9
NetC141_1: C141.1, Q7.1, Q9.1, R30.1, R35.1, R37.1, R41.1, R44.1
NetC141_2: C141.2, R35.2, R42.1
NetC142_1: C142.1, R42.2, R47.1, U1.6
NetCT1_2: CT1.2, J5.1
NetCT1_4: CT1.4, R83.1, R89.1
NetD1_1: D1.1, Q1.3, Q4.2, R2.1
NetD1_2: D1.2, Q1.1, Q2.1
NetD2_1: D2.1, D9.2, D9.3
NetD2_2: D2.2, D4.1
NetD5_3: D5.3, R45.1, R46.2
NetD8_1: D8.1, Q5.4, Q6.2, R22.1, R58.1, R59.1
NetD8_2: D8.2, Q6.3, R25.1
NetD9_1: D9.1, R13.1, VR1.1, VR2.1
NetD10_2: D10.2, R89.2
NetFB1_1: FB1.1, P1.1
NetFB2_1: FB2.1, P1.3
NetFB3_1: FB3.1, P1.5
NetJ2_1: J2.1, R78.1
NetP2_1: P2.1, Q12.3, R65.2, R70.1
NetP2_2: P2.2, Q13.3, R66.2, R71.1
NetP2_3: P2.3, R84.1
NetP3_3: P3.3, R67.2
NetP4_1: P4.1, R76.2
NetP4_3: P4.3, R77.2
NetQ3_1: Q3.1, Q4.1, R19.2
NetQ5_5: Q5.5, Q5.6, Q5.7, Q5.8, XF1.1
NetQ8_1: Q8.1, Q10.1, R28.2, R29.1, R34.1, R40.1, R43.1
NetQ11_1: Q11.1, U4.3, U4.4, U5.2
NetQ14_1: Q14.1, U4.10, U4.11, U5.3
NetQ15_1: Q15.1, U5.1, U5.5, U5.6
NetQ16_1: Q16.1, R78.2
NetQ16_3: Q16.3, R62.1, U3.3, U3.6, U3.9, U3.12, U5.9, U5.12
NetR14_2: R14.2, VR1.2
NetR17_2: R17.2, VR2.2
NetR27_2: R27.2, R28.1, U1.2
NetR46_1: R46.1, U2.3
NetR51_1: R51.1, R57.2, U2.2
NetR61_1: R61.1, U5.10
NetR63_1: R63.1, U5.13
NetR64_1: R64.1, U3.1
NetR69_1: R69.1, U3.4
NetR70_2: R70.2, R73.1
NetR71_2: R71.2, R74.1
NetR72_1: R72.1, U3.10
NetR75_1: R75.1, U3.13
NetR84_2: R84.2, U6.1, U6.2
NetU3_2: U3.2, U3.5, U3.8, U3.11, U5.4, U5.8, U5.11
NetU4_2: U4.2, U4.6
NetU4_8: U4.8, U4.12
RFB1: C20.2, C21.2, R26.1
RFB2: C19.2, C22.2, R24.1
RFIN: C34.1, R45.2, R48.2, R49.2
RFgnd: C60.1, CT1.5, CT1.6, J5.2, J5.3, J5.4, J5.5, MH6.1, P5.2, R86.2
SWRok: Q13.1, U4.13, U6.7
VAMP: C13.2, J3.1, J3.2, J3.3, J3.4, J3.5, J3.6, J3.7, J3.8, Q2.2, R16.1, R23.2, XF1.2
VN: C48.1, C49.1, C50.1, D5.1, FB2.2, R50.2, R52.2, R55.2, R56.1
VP: C45.1, C46.1, C47.1, D5.2, FB1.2, R1.2, R22.2, R31.2, R32.1, R33.2, R36.2, R58.2, R59.2
VSUP: J1.1, J1.2, J1.3, J1.4, J1.5, J1.6, J1.7, J1.8, Q1.2, Q2.3, Q3.2, R2.2, R3.2, R4.2, R5.2, R6.2, R7.2, R8.2, R9.2, R10.2, R11.2, R12.2, R88.1
Vd: C51.1, C52.1, C53.1, FB3.2, R60.1, R65.1, R66.1, R67.1, R68.1, R76.1, R77.1, R79.1, R81.1, R82.1, R85.1, R87.1, R93.1
ref2V5: R85.2, R91.1, U7.2, U8.1

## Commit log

2023-06-21 update
    Verbesserung dem Ausgangssignal
2023-06-21 Update Ausgangssignal
2023-06-23 Änderung
    Simulationszeit und Pulse
2023-06-23 create Folders
2023-06-23 push pull Stufe
2023-06-23 pushpull Erstellung
2023-06-23 Probe Simulation
2023-06-24 update
    test Simulation durchgeführt. Vp und Vin wurden geändert.
2023-06-24 update und simulation
2023-06-25 Notes
2023-06-25 Analyse
    Analyse text doc erstellt.
2023-06-25 update value
2023-06-25 Update Analyse.txt
    zusammenfassung
2023-06-27 Analyse
    Q3 und Q4 Differentialpaar. Differezverstärker
2023-06-27 update analyses
2023-06-28 analyse
2023-06-28 analyse update
2023-06-28 update
    Änderung der Schaltung
2023-07-17 Update lib
2023-07-31 update
    delete file
2023-07-31 new Simulation
2023-07-31 new mosfets
2023-10-02 Simulation rerun
2023-10-25 Kicad design
    nicht vollständig. Spannungsquelle muss noch mitreingefügt
2023-10-30 update sockets
2023-10-30 update ground plate
2023-10-30 update vin/vout
2023-10-30 Ground plate connected
2023-10-30 groundplate altered
    all the ground sockets are connected
2023-10-30 connection complete
2023-10-31 Vp1 socket
    install Vp1 socket
2023-11-01 new version update
2023-11-06 name change
2023-11-06 replace file
2023-11-06 version 6.0 and 7.0
2023-11-06 replace old file
2023-11-06 paste right copy
2023-11-07 update simulation
2023-11-08 new upload.
    correct versions
2023-11-13 Final results
2024-01-04 first OA simulated
    Simulation of the first part of the OA. with AD8021
2024-01-05 File Simulation
    Simulationen stufenweise gemacht. erste Stufe funktioniert. nicht inv / inv Stufen müssen noch geändert werden
2024-01-10 Simulation and Kicad update
    Simulation oof the Switch updated with an op amp. Kicad structure updated (0.2 version)
2024-01-10 files added
    description files added
2024-01-12 Switch Platine
    Platine 0.2 Entwurf mit OpV
2024-01-18 Simulation und PCB update
2024-01-22 4 stufige Simulation
2024-01-22 kicad switch LDO install
2024-01-23 HF part
    added the high frequency part to the simulation
2024-01-31 Simulation Update
    added high frequency part
2024-06-18 Update Simulation and Schematic
2024-07-01 Update
    KiCad Schaltplan und Footprints unter Ampilfier.
    Data Sheets zusammengefasst.
2024-07-03 update Ampilfier
    Schematic updated with separate pages.
    all footprints added.
    to do :
    HF Part
2024-07-07 Footprint created
    still needs work. embedded Pad design
2024-08-07 Platinenentwurf
    die Platine wurde aufgebaut. Kontrolle fehlt
2024-08-15 Update PCB
    update PCB
2024-08-29 Update PCB
    new design for the HF part
2024-09-01 update
    completed design and parts
2024-09-03 Amplifier2 Version 1.0
    PCB Design Ver 1.0 & List for Parts
2025-01-21 new Update
    latest simulations and PCB designs
2025-01-23 LTSpice Bib
